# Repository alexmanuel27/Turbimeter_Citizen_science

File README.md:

# Citizen-science turbidimeter

A compact optical instrument powered and controlled by an **Android USB-C
phone**, with no battery or built-in display.

Design: **Ing. Alex M. Rivera**. Updated **26 October 2026**.

**Building an instrument?** Start with the [step-by-step assembly and test
guide](docs/assembly.md). Fusion exports are in
[`3D/fusion-export/`](3D/fusion-export/).
For taking readings and calibrating the instrument, use the
[app user guide](docs/app-user-guide.md).

The prototype combines two stacked PCBs, an 850 nm infrared LED, two BPW34
photodiodes, an MCP6002, an ADS1115 and a XIAO SAMD21. The firmware measures
a dark-corrected scatter/reference **optical ratio**. Android version **0.5**
can convert that ratio using a calibration against a reference turbidimeter.

## Current status

| Part | Verified / available | Next step |
| --- | --- | --- |
| Electronics | Assembled prototype; ADS1115 acquisition and both optical channels respond on the Mac | Verify complete operation with water-filled cuvettes and compatible phones |
| Firmware | Real USB-CDC readings, dark subtraction, ratio and hardware-error reporting; LED on **D10** | Characterize response, noise and range across samples |
| Android | Real readings, reference calibration, marked extrapolation, local history, CSV and calibration JSON transfer | Validate calibration with a reference instrument and complete phone/release checks |
| Enclosure | Printed body/lid sources and assembled closed-enclosure bench tests | Confirm optical alignment, cable support and sealing in the finished instrument |
| Quantitative turbidity | Calibration workflow implemented | Obtain reference measurements, calibrate and validate independent samples |
| Citizen-science platform | Not implemented; app currently works offline | Define the platform and optional data-upload workflow |

On **26 October**, after wiring repairs and a direct XIAO-to-ADS ground jumper,
20 controller-only acquisitions completed without errors. The complete sensor,
with its **enclosure closed and an empty cuvette**, then completed **20/20**
measurements: mean optical ratio **6.902305**, short-run CV **0.0760%**.
This demonstrates repeatability under that condition, **not turbidity accuracy**.
Water-filled-cuvette testing is deferred; no zero-turbidity blank or usable
FNU/NTU range has been established. See the [bench records](firmware/xiao_samd21_turbimeter/bench/README.md).

The original 18 October target is retained as project history. Calibration and
independent validation are still required before community deployment.

## Repository map

| Folder | Purpose / entry point |
| --- | --- |
| [hardware/](hardware/README.md) | Sensor/base KiCad project: `esque.kicad_pro`; custom libraries and base manufacturing exports |
| [hardware-controller/](hardware-controller/README.md) | Independent controller/ADC KiCad project: `controller.kicad_pro`; local libraries, models and exports |
| [3D/](3D/README.md) | Current enclosure: `fusion-export/body_tur.stl`, `Tapa_tur.stl` |
| [firmware/xiao_samd21_turbimeter/](firmware/xiao_samd21_turbimeter/README.md) | Active XIAO firmware, wiring, upload instructions and recorded bench sessions |
| [android-app/](android-app/README.md) | Android app, calibration, tests and Google Play preparation |
| [docs/](docs/README.md) | Optical design, purchase list, BOM notes and privacy policy |
| [hardware/archive/](hardware/archive/) | Earlier electronic designs and retired manufacturing exports |
| [img/](img/) | Earlier prototype photos and animations; not current manufacturing references |

Open the base and controller as **separate KiCad 9 projects**. Their current
saved PCB files are the editable sources. Existing Gerbers, assembly renders
and older validation reports are revision snapshots; check their notes before
manufacturing. Repository organization preserves the saved PCB routing.

## Measurement chain

```mermaid
flowchart LR
    LED[850 nm LED] --> Sample[Cuvette]
    Sample --> Scatter[90° scatter photodiode]
    LED --> Reference[Shielded reference photodiode]
    Scatter --> Amplifier[MCP6002 dual amplifier]
    Reference --> Amplifier
    Amplifier --> ADC[ADS1115]
    ADC --> MCU[XIAO SAMD21]
    MCU <-->|USB CDC| Phone[Android app]
```

The cuvette has a **10 mm optical path** and a provisional **12.5 × 12.5 mm
exterior**. The reference photodiode monitors a fixed fraction of the LED light.
Each acquisition reads both channels with the LED off and on, subtracts the
dark readings, and divides corrected scatter by corrected reference.

The XIAO's regulated **3.3 V** rail supplies the ADC and analog circuit.
**D4 = SDA, D5 = SCL, D10 = LED control (KiCad A1 pin 11)**.
The LED uses resistive current limiting. The assembled prototype was reported
with **100 kΩ R1/R2**, whereas the schematic starting value was 1 MΩ; see the
[optical design notes](docs/optical-design.md) before replicating it.

**An optical ratio is not FNU/NTU.** Reference calibration and independent
validation are required. Repeatability alone does not establish accuracy,
water safety, ISO/EPA compliance or performance across different phones.

## Use the prototype

1. Upload the [active XIAO firmware](firmware/xiao_samd21_turbimeter/README.md).
   Verify a common ground and a 3.3 V ADS supply. Controller-only tests need
   the documented direct ground jumper.
2. Use a data-capable USB connection. On the Mac, `PING` checks the link;
   `RAW` inspects LED-off/on ADC counts, and `MEASURE` returns an optical ratio.
3. Build/install the [Android app](android-app/README.md) on a phone with
   **USB host/OTG** support, then use **Connect sensor → Measure now → History**.
4. Once a reference instrument is available, open **Calibration** and pair
   five sensor readings per sample with its reference value, for **3–12 points**.
   Check additional samples that were not used to fit the curve.

The app joins calibration points with straight lines. Outside the measured
range it extends the nearest end segment and marks the estimate
**EXTRAPOLATED**. Curves belong to the sensor's USB identity. History retains
UTC time, optical ratio and calibration ID; CSV and calibration JSON can be
exported. A replacement XIAO has a different identity and needs its own curve.

**This release has no online upload, contributor form or location capture.**
USB 2.0 uses VBUS, GND, D− and D+; USB-C role detection must also be handled
by suitable plugs or an OTG adapter. Four wires alone do not establish phone
compatibility. Earlier carrier USB links are historical; check the saved
boards and actual cable termination in the [hardware notes](hardware/README.md).

## Procurement and development

The current [English purchase workbook](docs/shopping-list-prototype-usb-c.xlsx)
is the latest user-edited copy, consolidated under `docs/`. It contains direct
supplier links; prices have **not** been refreshed during this repository
update. Read the [BOM revision notes](docs/BOM.md) before ordering. The earlier
29 September workbook is retained in [docs/archive/](docs/archive/).

Build and software-check instructions are in the [Android README](android-app/README.md).
Publication tasks are in the [Google Play checklist](android-app/play-store/release-checklist.md).
Build outputs, signing keys, tester addresses, IDE settings and local SDK paths
are excluded from Git. APKs/AABs are generated locally; they are not release
artifacts published by this commit.

The [SEN0189 sketch](firmware/legacy_sen0189/),
[experimental Nano/TL072 sketch](firmware/firmware.ino) and
[legacy firmware notes](docs/firmware.md) are historical references, not the
active XIAO implementation.

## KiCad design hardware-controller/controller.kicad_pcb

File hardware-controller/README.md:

# Standalone controller / ADC project

Design: **Ing. Alex M. Rivera**. Separated **19 October 2026**.

**Current source, 26 October:** the saved PCB includes subsequent builder
routing and placement changes. The dated sections below record earlier work;
their counts, positions and checks must not be read as a validation of later
edits. Existing [Gerbers](gerber/README.md) and assembly previews are snapshots.
The repository organization preserves this project and its routing unchanged.

Open **[controller.kicad_pro](controller.kicad_pro)** directly in KiCad 9.
The schematic and PCB have the same basename so KiCad opens the correct pair.
This folder is independent of the sensor/base project: its custom symbols,
footprints, required 3D models and Gerber output directory are local.
It uses the standard libraries and 3D models supplied with KiCad 9.

| Location | Contents |
| --- | --- |
| `controller.kicad_sch` | Existing controller schematic |
| `controller.kicad_pcb` | User's current PCB, including tracks and zone fills |
| `controller.kicad_pro` | Project settings and design rules |
| `Turbimeter.kicad_sym`, `Turbimeter.pretty/` | Project-local custom libraries |
| `3dmodels/` | Required supplied/derived module models |
| `gerber/` | Existing controller exports, moved as supplied; destination for new plots |

The separation preserves schematic contents, board geometry, component
positions, nets, tracks, zones and design rules. Only library/model lookup
paths and the plot-output directory were changed. The sensor/base project
was left untouched. The folder can be moved with its contents without
requiring the sensor project's libraries.

The existing design is still work in progress. Before moving, its DRC report
contained 2 findings, 2 unconnected items and 2 schematic-parity findings.
Separation does not repair or approve those existing findings. The older
assembly previews and alignment report describe a previous placement revision;
use this PCB as the current editable source and regenerate fabrication outputs
after completing your checks.

## J1 alignment — 20 October 2026, revision 0.11

Design: **Ing. Alex M. Rivera**.

J1 is now a **male SMD 1×6 header, 2.54 mm pitch**, on **F.Cu** (the
controller's underside), to mate with the female connector on the base.
Its footprint is
`Connector_PinHeader_2.54mm:PinHeader_1x06_P2.54mm_Vertical_SMD_Pin1Right`.
The schematic uses the same footprint. Both boards share the same XY frame.

| Contact | X (mm) | Y (mm) | Signal |
| --- | --- | --- | --- |
| 1 | 20.375 | 23.545 | GND |
| 2 | 20.375 | 26.085 | 3V3 |
| 3 | 20.375 | 28.625 | LED_DRIVE |
| 4 | 20.375 | 31.165 | SCATTER_OUT |
| 5 | 20.375 | 33.705 | REFERENCE_OUT |
| 6 | 20.375 | 36.245 | GND |

The footprint origin is **X 20.375, Y 29.895 mm, rotation 0°**. These are
the mating contact axes; the SMD solder pads alternate to either side.
All six contact axes and schematic net assignments were checked against
the saved base. The base file, other controller placements and all 49 existing
track/via items were preserved. Zone fills were cleared for the changed pads.

**Routing and fabrication checks remain pending.** Old J1 traces now cross
new pads on other nets and must be rerouted before powering the board.
Pad 2 has only **0.0607 mm copper-to-edge clearance**, below the project's
0.5 mm rule; resolve this with a mechanically verified connector land pattern
or a local upper-board outline change before fabrication. The outline has
been preserved. Ensure the base socket faces the controller header during
assembly: its current F-side model conflicts with the earlier B-side-up base
mounting convention. Through-hole placement must follow the actual assembly.

The existing Gerbers and assembly previews predate this change. Refill zones,
run DRC and regenerate fabrication outputs after routing.

## M3 mounting hole — 25 October 2026, revision 0.12

Design: **Ing. Alex M. Rivera**.

H1 is aligned with the large via on the base at **X 47.680, Y 36.930 mm**.
Its **3.000 mm non-plated hole** matches the base drill exactly; the controller
reserves a **5.000 mm diameter free of copper**. It is a mechanical mounting
hole and has no electrical net. Its local footprint is
`Turbimeter:MountingHole_3mm_M3`. Confirm that the actual M3 screw passes
through the nominal 3 mm hole before assembly.

Existing component placements, tracks, vias and outline were preserved. The
ground zone was refilled to clear H1. DRC introduced no new findings; the
existing design findings remain to be resolved. The base was not modified.
Regenerate manufacturing files after completing the design.

## Standalone controller test — 26 October 2026

Design: **Ing. Alex M. Rivera**.

The current F.Cu ground fill has two islands: XIAO A1 pin 13 / C5 / J1 pin 1,
and ADS1115 U2 pins 2 and 5 / J1 pin 6. The base's ground plane normally joins
J1 pins 1 and 6. When testing this board **without the base**, fit a short
direct **XIAO GND to ADS GND jumper** with USB disconnected, and confirm
ADS VDD is 3.3 V before reconnecting. Do not rely on the mechanical screw as
an electrical ground return.

Adding that jumper resolved the observed I2C/acquisition blocking on the
assembled standalone controller: 20 consecutive `RAW` requests succeeded
using the normal D10 firmware. See the [bench record](../firmware/xiao_samd21_turbimeter/bench/2026-10-26-controller-only-summary.json).
Analog/optical validation requires the sensor/base. PCB routing was not
changed in this diagnostic session.

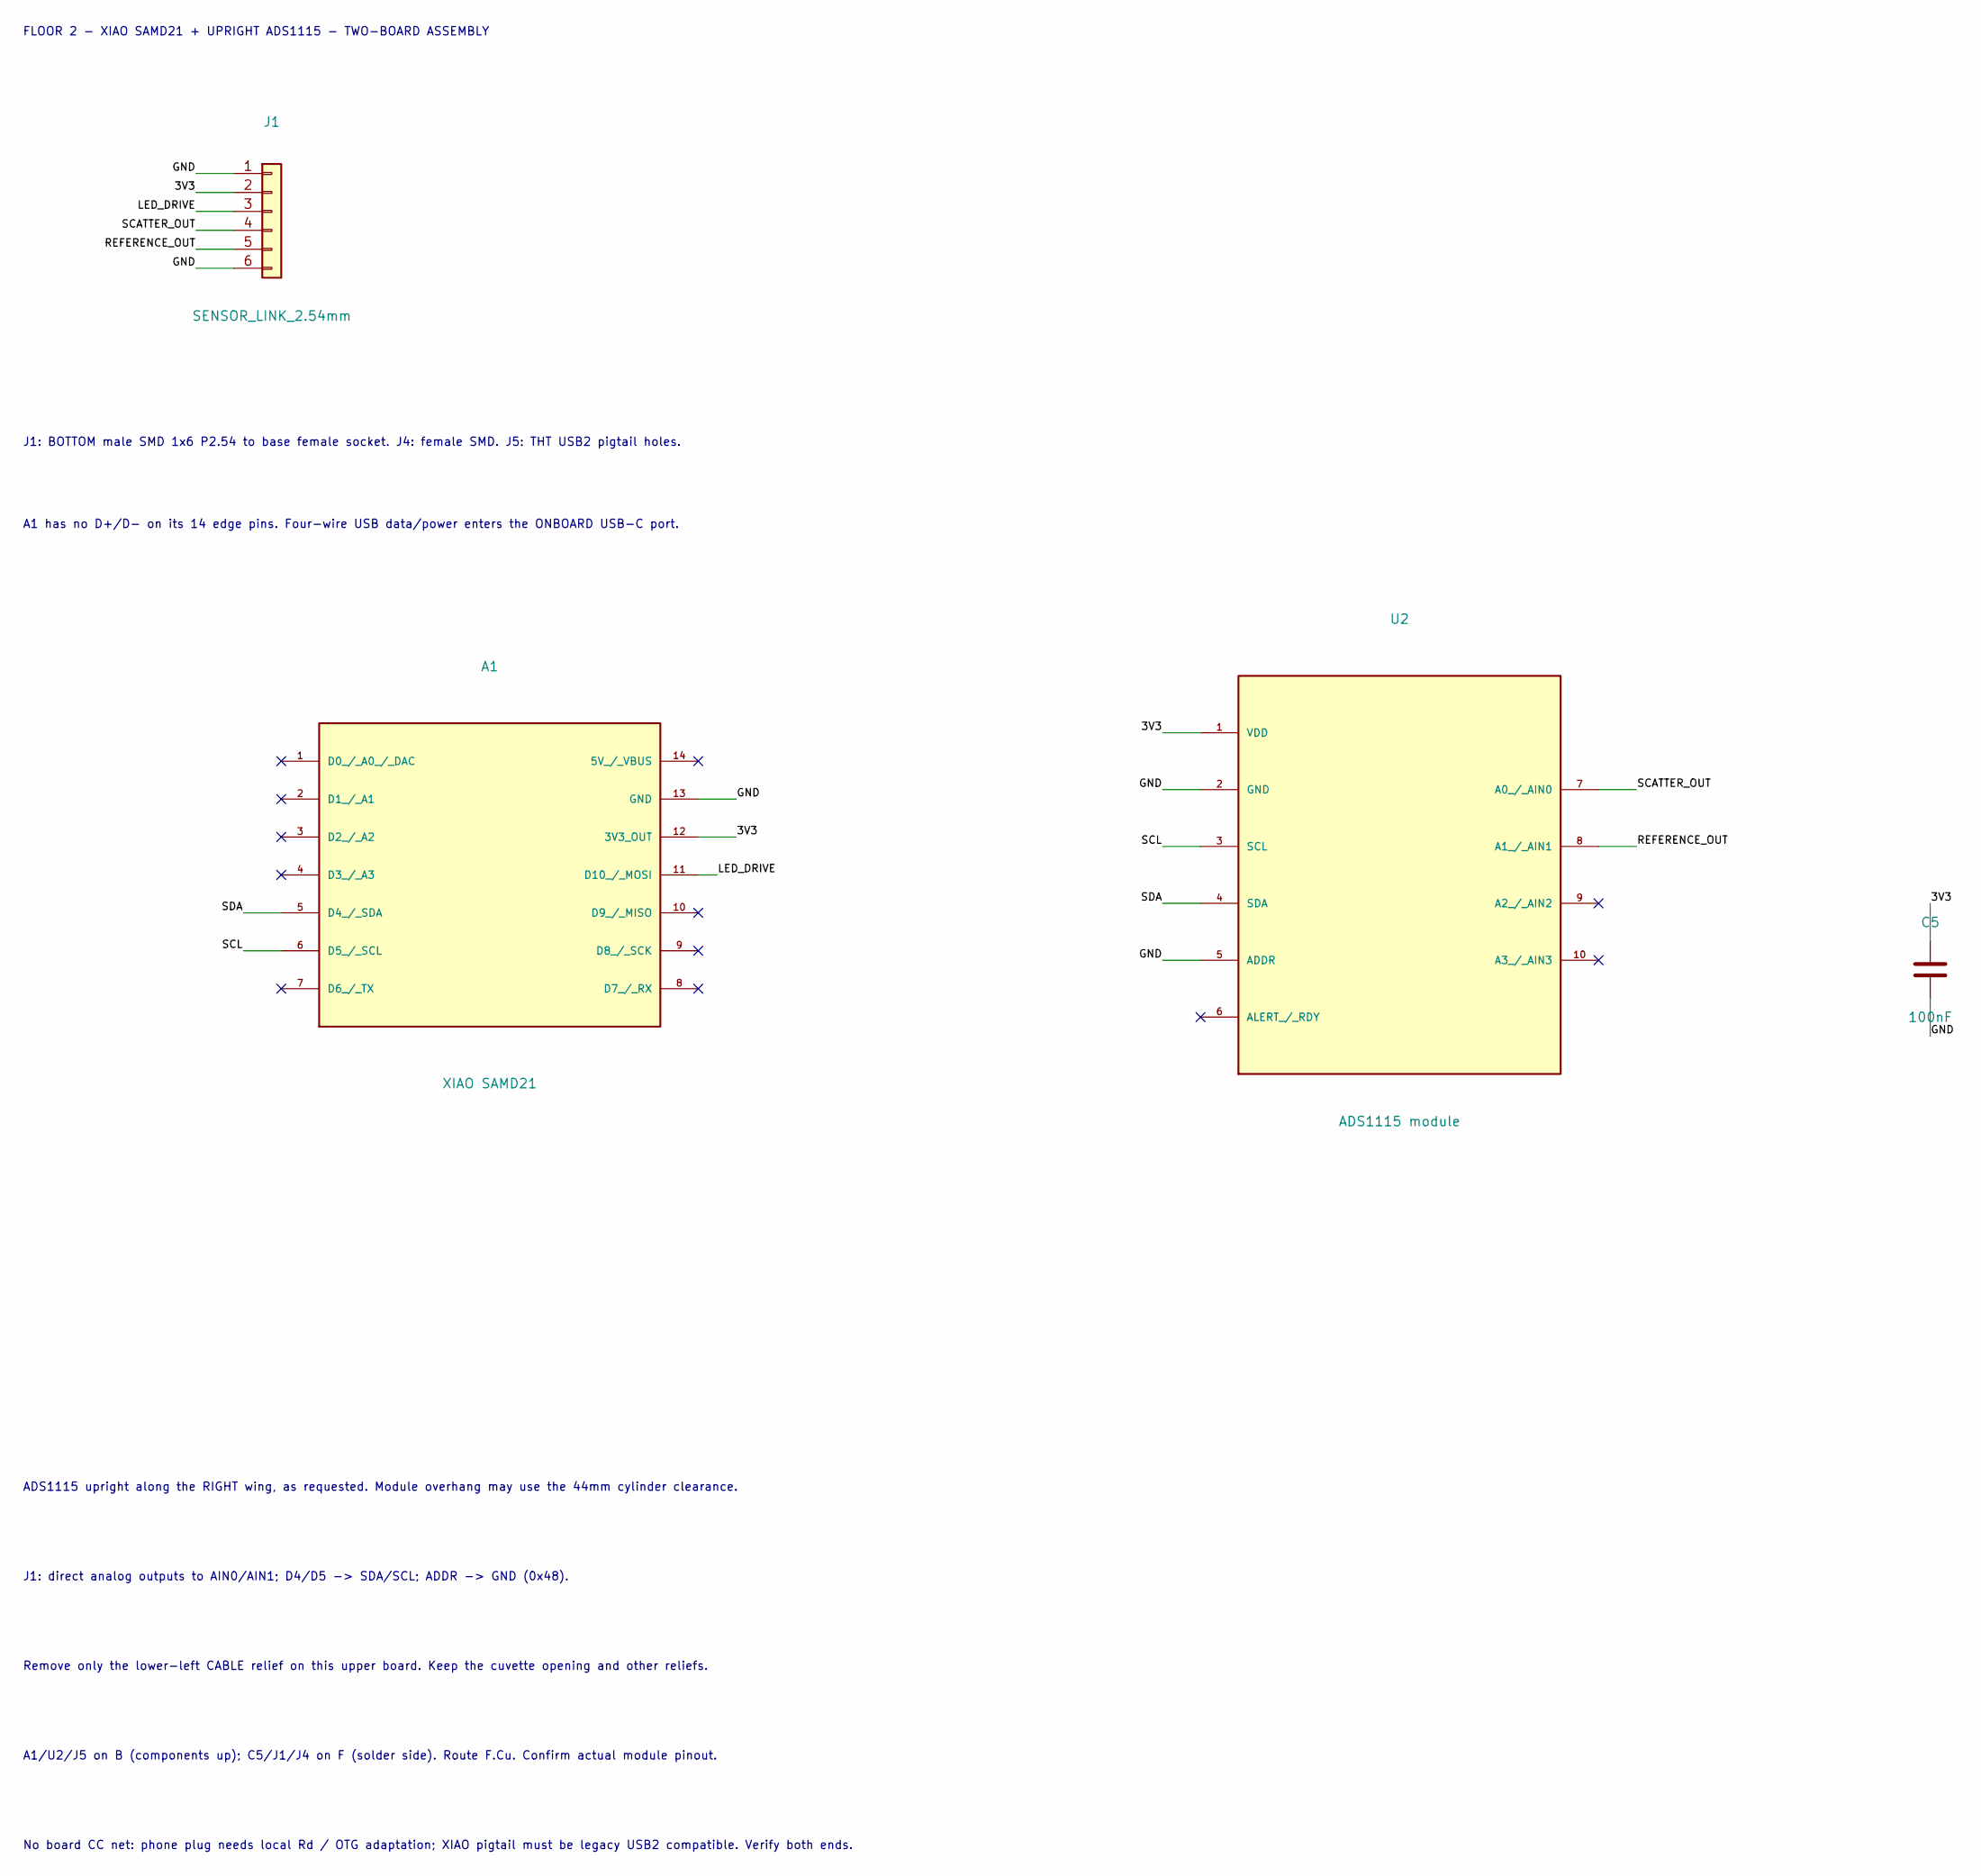
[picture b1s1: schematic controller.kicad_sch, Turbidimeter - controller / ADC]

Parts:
A1: XIAO SAMD21; XIAO_SAMD21_Upper_v08
C5: 100nF; C_Disc_D5.0mm_W2.5mm_P2.50mm
J1: SENSOR_LINK_2.54mm; PinHeader_1x06_P2.54mm_Vertical_SMD_Pin1Right
U2: ADS1115 module; ADS1115_Upright_v08

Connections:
/3V3: A1.12 (3V3_OUT), C5.1, J1.2, U2.1 (VDD)
/GND: A1.13 (GND), C5.2, J1.1, J1.6, U2.2 (GND), U2.5 (ADDR)
/LED_DRIVE: A1.11 (D10_/_MOSI), J1.3
/REFERENCE_OUT: J1.5, U2.8 (A1_/_AIN1)
/SCATTER_OUT: J1.4, U2.7 (A0_/_AIN0)
/SCL: A1.6 (D5_/_SCL), U2.3 (SCL)
/SDA: A1.5 (D4_/_SDA), U2.4 (SDA)

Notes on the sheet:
A1/U2/J5 on B (components up); C5/J1/J4 on F (solder side). Route F.Cu. Confirm actual module pinout.
FLOOR 2 - XIAO SAMD21 + UPRIGHT ADS1115 - TWO-BOARD ASSEMBLY
Remove only the lower-left CABLE relief on this upper board. Keep the cuvette opening and other reliefs.
ADS1115 upright along the RIGHT wing, as requested. Module overhang may use the 44mm cylinder clearance.
A1 has no D+/D- on its 14 edge pins. Four-wire USB data/power enters the ONBOARD USB-C port.
J1: BOTTOM male SMD 1x6 P2.54 to base female socket. J4: female SMD. J5: THT USB2 pigtail holes.
No board CC net: phone plug needs local Rd / OTG adaptation; XIAO pigtail must be legacy USB2 compatible. Verify both ends.
J1: direct analog outputs to AIN0/AIN1; D4/D5 -> SDA/SCL; ADDR -> GND (0x48).

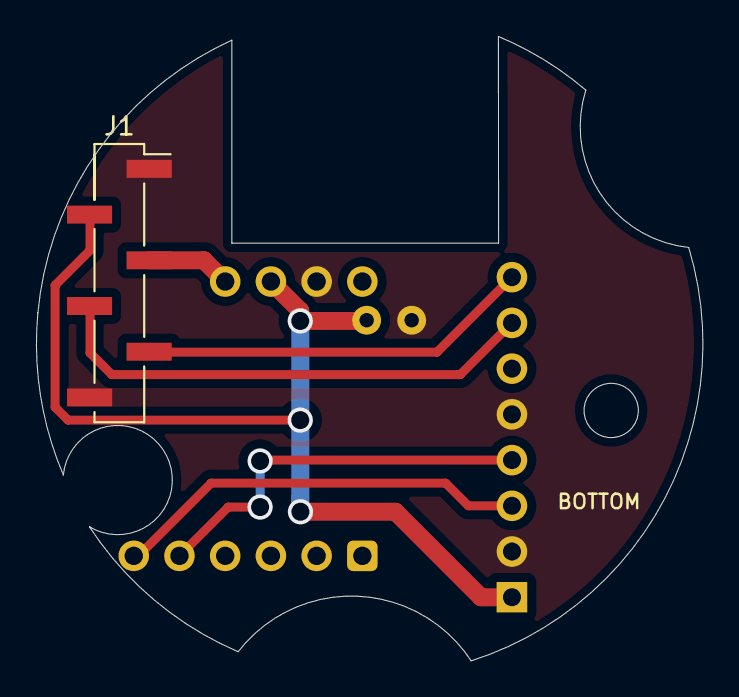
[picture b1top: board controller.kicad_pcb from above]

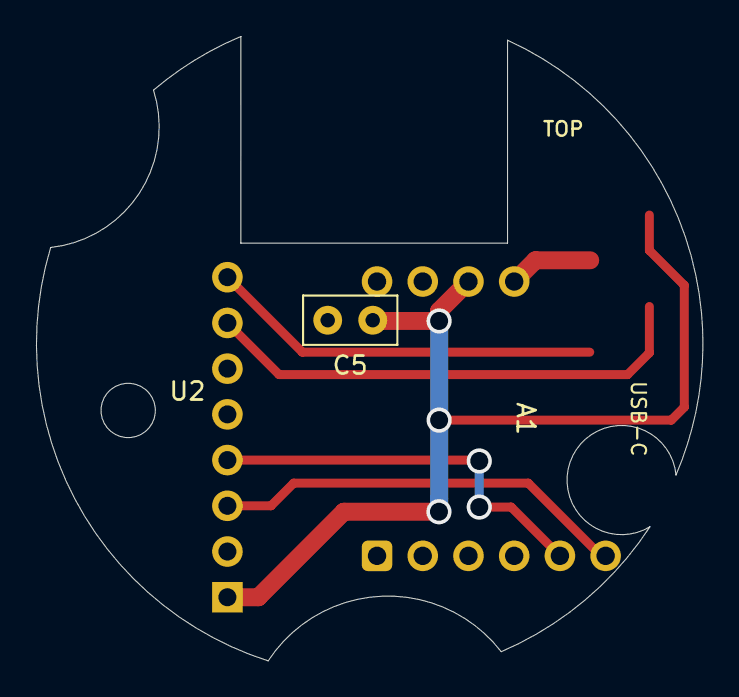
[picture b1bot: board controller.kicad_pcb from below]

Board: 2 copper layers, 37.0 x 34.7 mm, 4 parts (3 on the bottom side), 7 nets.

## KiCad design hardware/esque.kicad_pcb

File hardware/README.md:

# Sensor/base electronics and two-board assembly

Design: **Ing. Alex M. Rivera**. Updated **26 October 2026**.

| Board | Active KiCad 9 project | Current source |
| --- | --- | --- |
| Sensor/base | [esque.kicad_pro](esque.kicad_pro) | Builder's saved schematic and routed PCB |
| Controller + ADS1115 | [../hardware-controller/controller.kicad_pro](../hardware-controller/controller.kicad_pro) | Independent project; builder's saved routing and subsequent edits |

Open these as separate projects. Their saved PCB files take precedence over
older placement tables, title-block notes, renders and manufacturing exports.
The 26 October repository organization preserves the PCB/schematic/project
files byte for byte; it does not reroute or approve either board.

## Current electrical and bench notes

- J1 is now **1×6 at 2.54 mm pitch**. Base: through-hole female socket;
  controller: SMD male header on F. See the
  [controller revision notes](../hardware-controller/README.md).
- J1 nets, in pin order: **GND, 3V3, LED_DRIVE, SCATTER_OUT,
  REFERENCE_OUT, GND**. Check the saved pad geometry and actual connector
  engagement; earlier 2.00 mm placement tables below are obsolete.
- **LED_DRIVE uses XIAO D10 (KiCad A1 pin 11)**. D4/D5 carry I²C.
  ADS1115 and MCP6002 use 3.3 V and a common ground.
- The builder fitted **100 kΩ R1/R2** during bench tests; the original
  schematic assumption was 1 MΩ. Nominal VREF is 1.65 V; approximately
  1.6 V was reported after repair.
- Standalone controller testing needs a direct **XIAO GND ↔ ADS GND** jumper:
  the controller's two ground islands otherwise rely on the base connection.
  See the [firmware wiring notes](../firmware/xiao_samd21_turbimeter/README.md).
- The saved boards have subsequent user edits, including removal of the
  earlier USB connector footprints. The J2/J4/J5 cable chain below is a
  **historical layout**, not the current board inventory. USB data enters
  the XIAO through its USB socket; verify the actual cable termination.

The assembled closed instrument produced real uncalibrated optical ratios on
the Mac. [Bench records](../firmware/xiao_samd21_turbimeter/bench/README.md)
document the setups and limits. This does not certify the saved design or its
exports as ready for replication or quantitative measurement.

## Drawings, manufacturing and checks

- [Base export notes](gerber/README.md) and
  [controller export notes](../hardware-controller/gerber/README.md).
- [Assembly renders](renders/README.md), [board preview](pcb-top-preview.svg)
  and [connected drawing](stack-assembly.svg) predate later placement edits.
- [Revision 0.10 validation report](validation.md) records the 13 October
  design, not the latest saved files. `check_stack.py` contains those earlier
  layout assumptions and is not a current release gate.
- [BOM notes](../docs/BOM.md) identify purchasing and as-built differences.

## Historical placement notes — revision 0.10, 13 October 2026

Everything below describes that earlier alignment. In particular, connector
pitch, inventory, coordinates, routing counts and validation claims are
historical. Use the active projects above for the present design.

## Mounting faces

The revised base uses **B for through-hole components** and **F for SMD**.
The upper board follows that physical orientation:

| Physical face in the assembled instrument | Native KiCad face | Upper components |
| --- | --- | --- |
| UP, away from the board below | B | XIAO A1, upright ADS1115 U2, J5 wire heads |
| BELOW, solder side | F | Female SMD sockets J1/J4, C5, through-hole solder joints |

Route the **upper PCB on F.Cu only**. Its soldering remains on one physical
face. KiCad retains conventional plated through-hole annuli on both logical
copper layers. Export the selected manufacturing layer after routing checks.

The base currently contains **86 F.Cu segments, 7 B.Cu segments and one F.Cu
zone**, as supplied. This alignment does not change or approve that routing.
Its existing TOP/BOTTOM legends and revision text were also preserved; use
the actual F/B component layers when interpreting assembly faces.

## Mechanical matching

The original base contour remains intact. The upper outline matches it except
for filling the lower-left USB cable relief; both retain the cuvette opening.
The nominal cuvette exterior is **12.5 × 12.5 mm**. A 44 mm Dwgs.User circle
marks the available enclosure diameter and is not a milling line.

All coordinates below are the **shared native KiCad coordinates**. Viewing
from the physical B side mirrors the drawing.

| Upper part | Position, mm | Native orientation | Purpose |
| --- | --- | --- | --- |
| J1 | 21.17175, 29.020 | 0°, F | Six mating contact axes match base J1 |
| J4 | 32.20675, 47.185 | 0°, F | Four mating contact axes match base J4 |
| A1 | 31.500, 37.500 | 90°, B | XIAO, USB toward the left in shared coordinates |
| U2 | 43.500, 44.660 | 90°, B | Upright ADS1115 on the right wing |
| J5 | 38.200, 47.600 | 180°, B | Accessible wire holes below the XIAO body |
| C5 | 40.000, 32.000 | 180°, F | 100 nF decoupling under the module |

Keep **J1/J4 mating axes fixed** while routing. SMD solder-pad centres are
offset from the socket contact axes. All ten contacts were checked by pin
number and net against the base.

J4 uses a local copy of the standard KiCad 2×2 P1.27 SMD socket footprint.
Three silk segments were moved to Fab to clear nearby XIAO pads; contact
geometry and 3D model are unchanged. The schematic references that local copy.

### Stack height

The provisional spacing is **14 mm between corresponding PCB faces**, or a
12.4 mm clear gap for 1.6 mm boards. With roughly 19 mm of upright ADS1115
above the upper board and 1 mm beneath the base, the nominal total is
**35.6 mm**. Allow approximately **36–38 mm before lid and cable clearance**.
The preferred 35 mm total has not been verified.

Select actual long-reach male headers, compatible SMD sockets and module
supports. Trim and insulate tails as required. Verify real optical bodies,
connector insertion, USB plug and cable bends with the printed enclosure.

## Electrical connections

| Interboard connector | Pin order, identical across both boards |
| --- | --- |
| J1 — 1×6, 2.00 mm | 1 GND; 2 3V3; 3 LED_DRIVE; 4 SCATTER_OUT; 5 REFERENCE_OUT; 6 GND |
| J4 — 2×2, 1.27 mm | 1 USB_VBUS; 2 GND; 3 USB_DM; 4 USB_DP |

Base J1 pin 1 is at **21.17175, 24.020 mm**; subsequent contacts advance +Y
by 2 mm. Base J4 pin 1 is at **32.84175, 46.550 mm**; pin 2 is 1.27 mm to
the left, and the second row advances +Y by 1.27 mm.

**The cable wire-hole numbering differs between boards after the user's
base revision. Follow net names, not matching hole numbers:**

| Wire hole | Base J2 | Upper J5 |
| --- | --- | --- |
| 1 | USB_DM (D−) | USB_VBUS |
| 2 | USB_DP (D+) | GND |
| 3 | USB_VBUS | USB_DM (D−) |
| 4 | GND | USB_DP (D+) |

J2/J5 are bare 1 mm through-holes in a 2×2 group at 2 mm pitch. Insert wires
from the component side and solder on the opposite side. Secure both cables
mechanically so that their joints carry no cable load.

The USB path is **phone → cable/OTG termination → base J2 → J4 → upper J5
→ compact USB-C male pigtail → XIAO socket**. The XIAO edge pins do not expose
D+/D−; edge pin 14 remains unconnected because it is after the protection diode.

No carrier CC net exists. A phone-facing captive/legacy plug needs suitable
local Rd termination or a proper OTG adapter; a normal C-to-C cable cannot
lose its CC path and still be assumed to work. The micro-facing plug must be
legacy USB2-compatible. Verify actual plug construction, continuity and both
phone orientations. See [Chromium's cable guide](https://chromium.googlesource.com/playground/chromium-org-site/+/refs/heads/main/chromium-os/cable-and-adapter-tips-and-tricks/index.md).

The left-facing XIAO socket has a provisional compact plug-tail allowance,
not a verified moulded-plug fit. Keep D+/D− short and together, with a sound
return path and away from high-impedance analog wiring.

J1 feeds U2 AIN0 (scatter) and AIN1 (reference). XIAO D4/D5 provide SDA/SCL;
ADDR is grounded for address `0x48`. The 3.3 V rail supplies the analog circuit.
Gain, LED current, noise, saturation and phone independence require bench tests.
The supplied ADS model prints a different analog-pin order; verify the actual
module. No pin mapping was changed to match a generic 3D asset.

## Checks and renders

Check the upper board against the current base:

```sh
/Applications/KiCad/KiCad.app/Contents/Frameworks/Python.framework/Versions/3.9/bin/python3 hardware/check_stack.py --match-base
```

This mode checks upper ERC, DRC, schematic parity, the module envelope and
all mating contacts. It permits unfinished upper routing and does **not**
approve base DRC findings. The older all-board check describes the earlier
unrouted, B.Cu fabrication stage and is not the current alignment check.

[3D model notes](3dmodels/README.md) describe the supplied assets and their
limits. The enclosure meshes named in this historical section have been superseded;
see the [current Fusion exports](../3D/README.md). The renders show individual boards and the connected stack, with
the B component faces physically upwards. They do not include the enclosure
or prove sealing, module dimensions or a complete cable fit.

Regenerate the views with KiCad Python:

```sh
/Applications/KiCad/KiCad.app/Contents/Frameworks/Python.framework/Versions/3.9/bin/python3 hardware/render_assembly.py
```

The supplied source models remain unchanged. [BOM notes](../docs/BOM.md)
list unpriced connectors and replacements. Generate final fabrication outputs
only after routing and fit checks; calibrate and validate before reporting
quantitative turbidity.

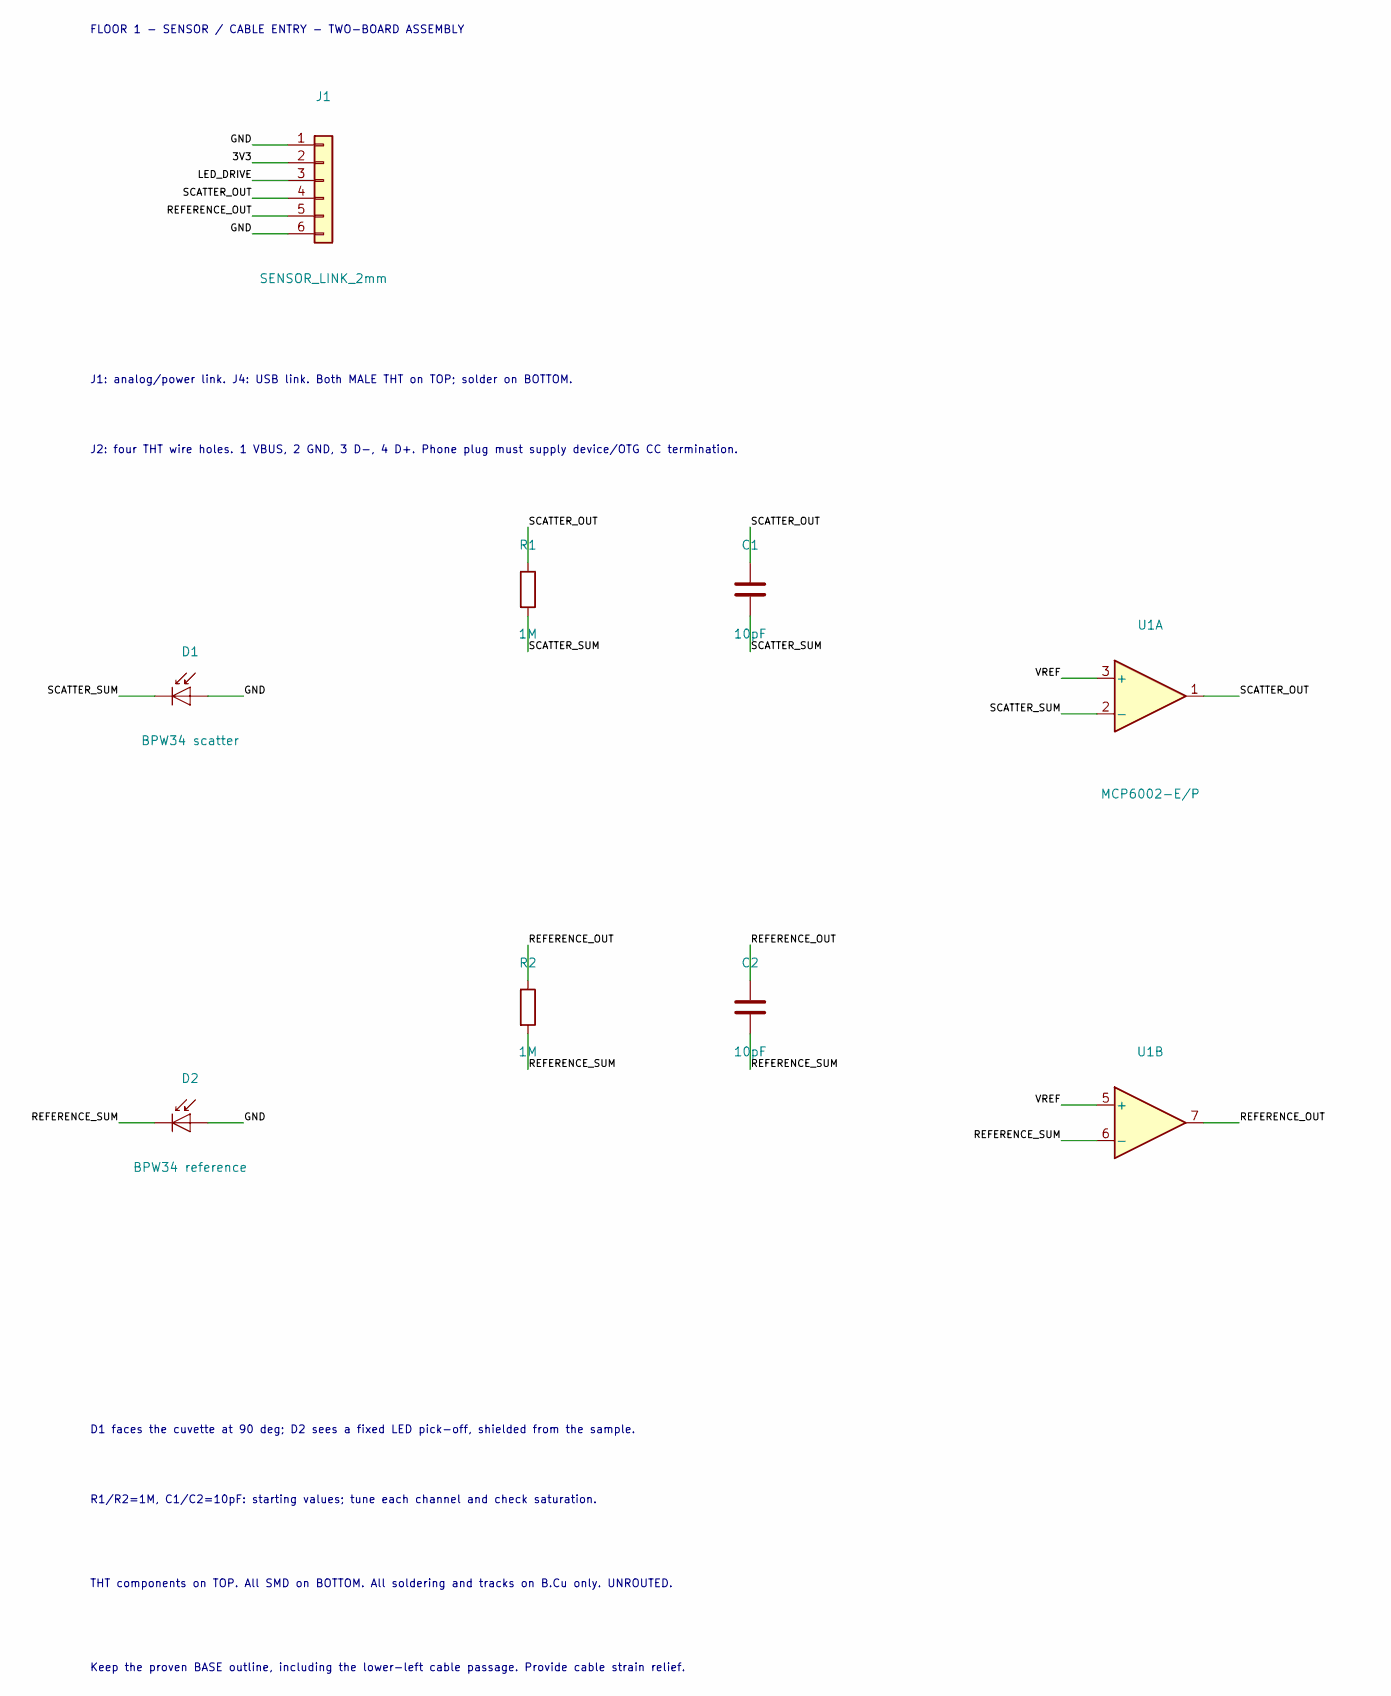
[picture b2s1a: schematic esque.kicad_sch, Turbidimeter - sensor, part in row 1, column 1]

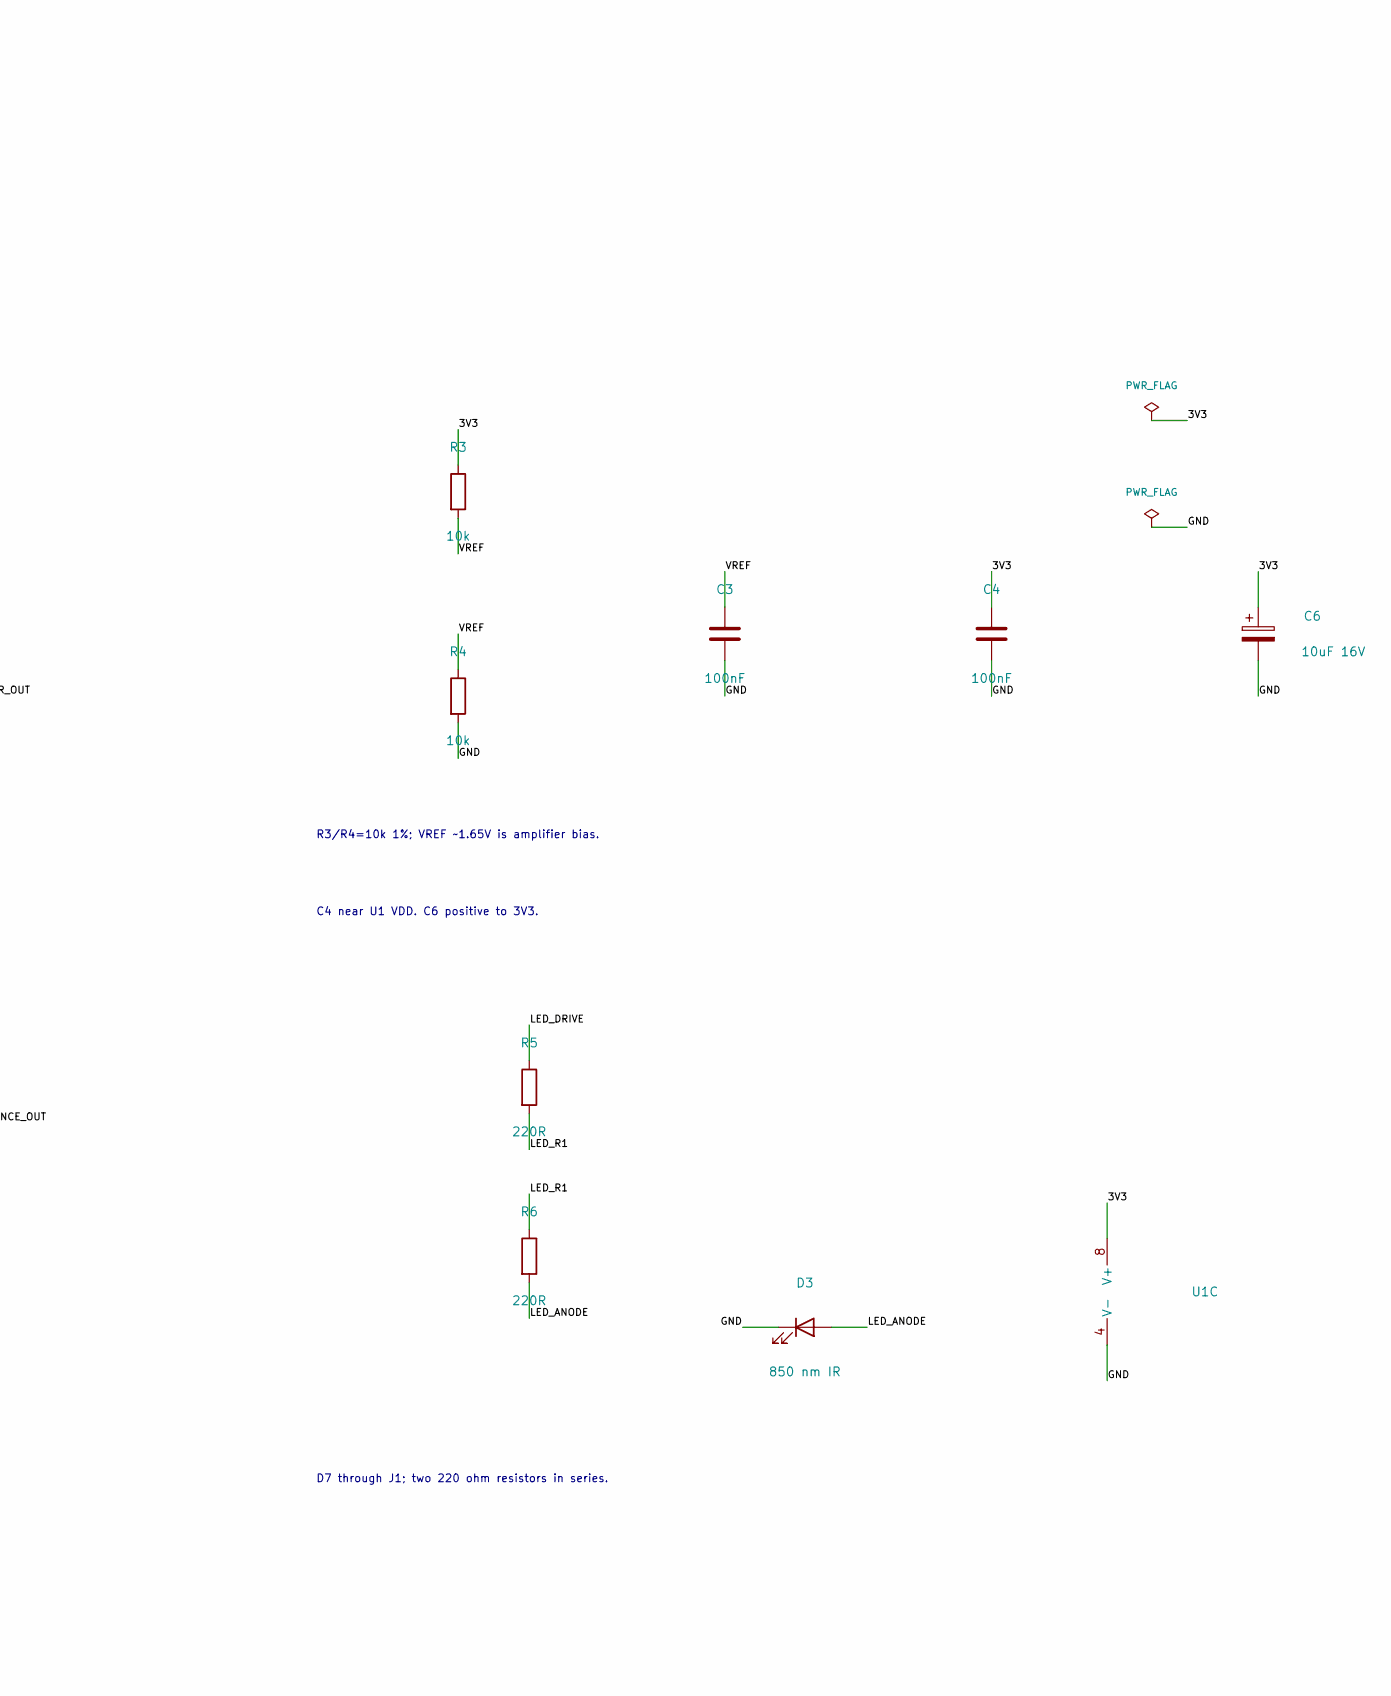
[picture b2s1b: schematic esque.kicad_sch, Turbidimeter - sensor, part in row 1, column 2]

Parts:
C1, C2: 10pF; C_Disc_D5.0mm_W2.5mm_P2.50mm
C3, C4: 100nF; C_Disc_D5.0mm_W2.5mm_P2.50mm
C6: 10uF 16V; CP_Radial_D5_P2_SingleFace
D1: BPW34 scatter; BPW34_Holder_v08
D2: BPW34 reference; BPW34_Holder_v08
D3: 850 nm IR; LED850_LeadPads_P2.54mm
J1: SENSOR_LINK_2mm; PinSocket_1x06_P2.54mm_Vertical
R1, R2: 1M; R_1206_3216Metric
R3, R4: 10k; R_1206_3216Metric
R5, R6: 220R; R_1206_3216Metric
U1: MCP6002-E/P; MCP6002_DIP8_SingleFace

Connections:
/3V3: C4.1, C6.1, J1.2, R3.1, U1.8 (V+)
/GND: C3.2, C4.2, C6.2, D1.2 (A), D2.2 (A), D3.1 (K), J1.1, J1.6, R4.2, U1.4 (V-)
/LED_ANODE: D3.2 (A), R6.2
/LED_DRIVE: J1.3, R5.1
/LED_R1: R5.2, R6.1
/REFERENCE_OUT: C2.1, J1.5, R2.1, U1.7
/REFERENCE_SUM: C2.2, D2.1 (K), R2.2, U1.6 (-)
/SCATTER_OUT: C1.1, J1.4, R1.1, U1.1
/SCATTER_SUM: C1.2, D1.1 (K), R1.2, U1.2 (-)
/VREF: C3.1, R3.2, R4.1, U1.3 (+), U1.5 (+)

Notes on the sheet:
Keep the proven BASE outline, including the lower-left cable passage. Provide cable strain relief.
R1/R2=1M, C1/C2=10pF: starting values; tune each channel and check saturation.
J2: four THT wire holes. 1 VBUS, 2 GND, 3 D-, 4 D+. Phone plug must supply device/OTG CC termination.
FLOOR 1 - SENSOR / CABLE ENTRY - TWO-BOARD ASSEMBLY
D7 through J1; two 220 ohm resistors in series.
THT components on TOP. All SMD on BOTTOM. All soldering and tracks on B.Cu only. UNROUTED.
D1 faces the cuvette at 90 deg; D2 sees a fixed LED pick-off, shielded from the sample.
J1: analog/power link. J4: USB link. Both MALE THT on TOP; solder on BOTTOM.
C4 near U1 VDD. C6 positive to 3V3.
R3/R4=10k 1%; VREF ~1.65V is amplifier bias.

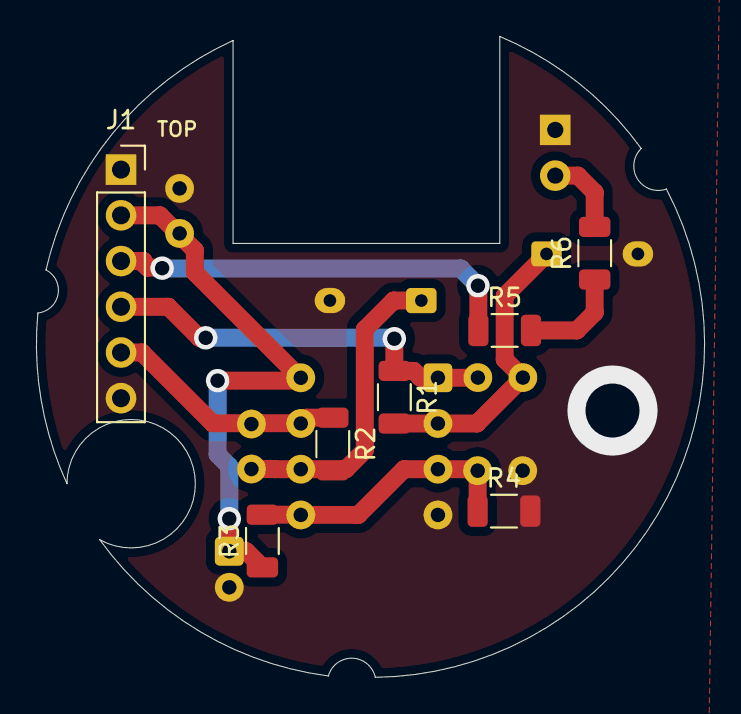
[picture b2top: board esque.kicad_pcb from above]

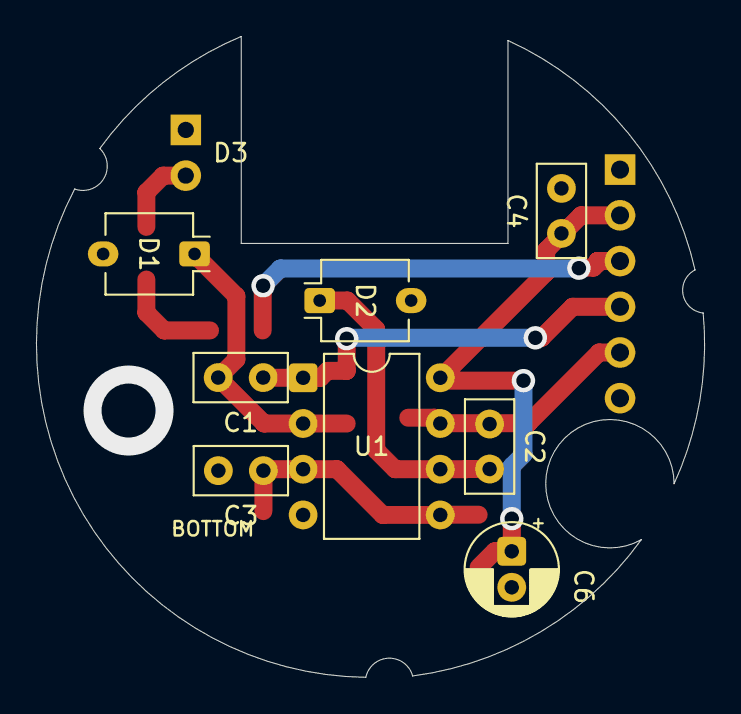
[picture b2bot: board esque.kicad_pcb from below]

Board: 2 copper layers, 37.1 x 35.6 mm, 16 parts (9 on the bottom side), 10 nets.
